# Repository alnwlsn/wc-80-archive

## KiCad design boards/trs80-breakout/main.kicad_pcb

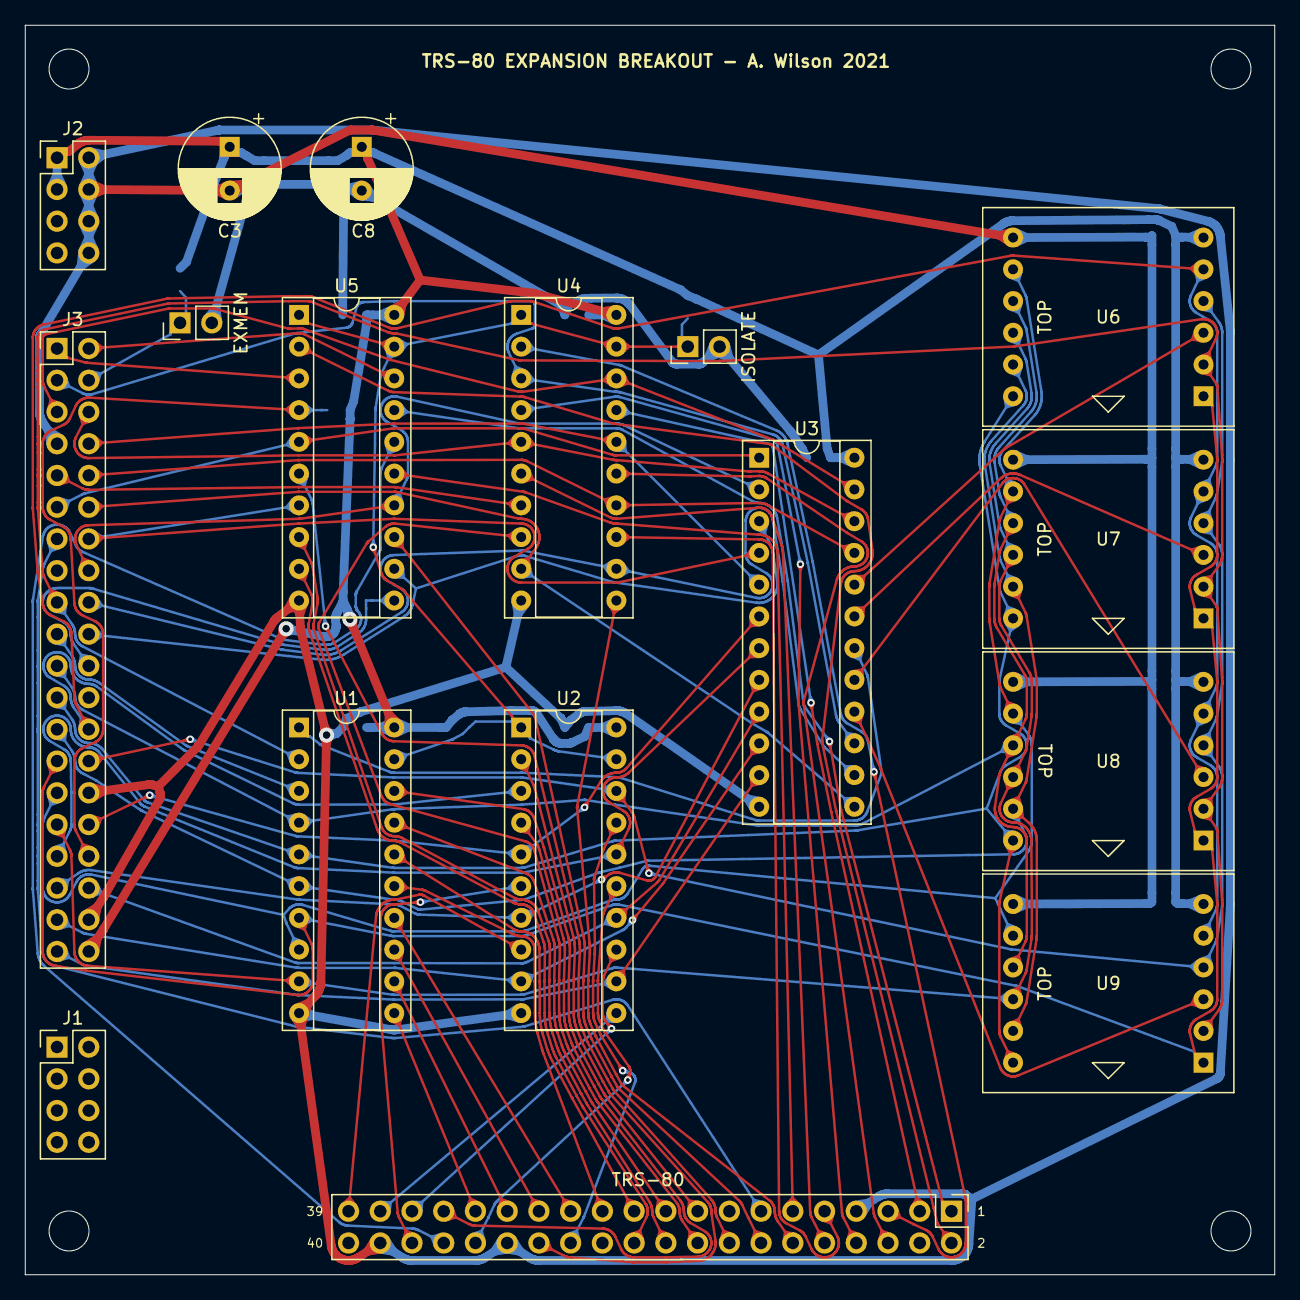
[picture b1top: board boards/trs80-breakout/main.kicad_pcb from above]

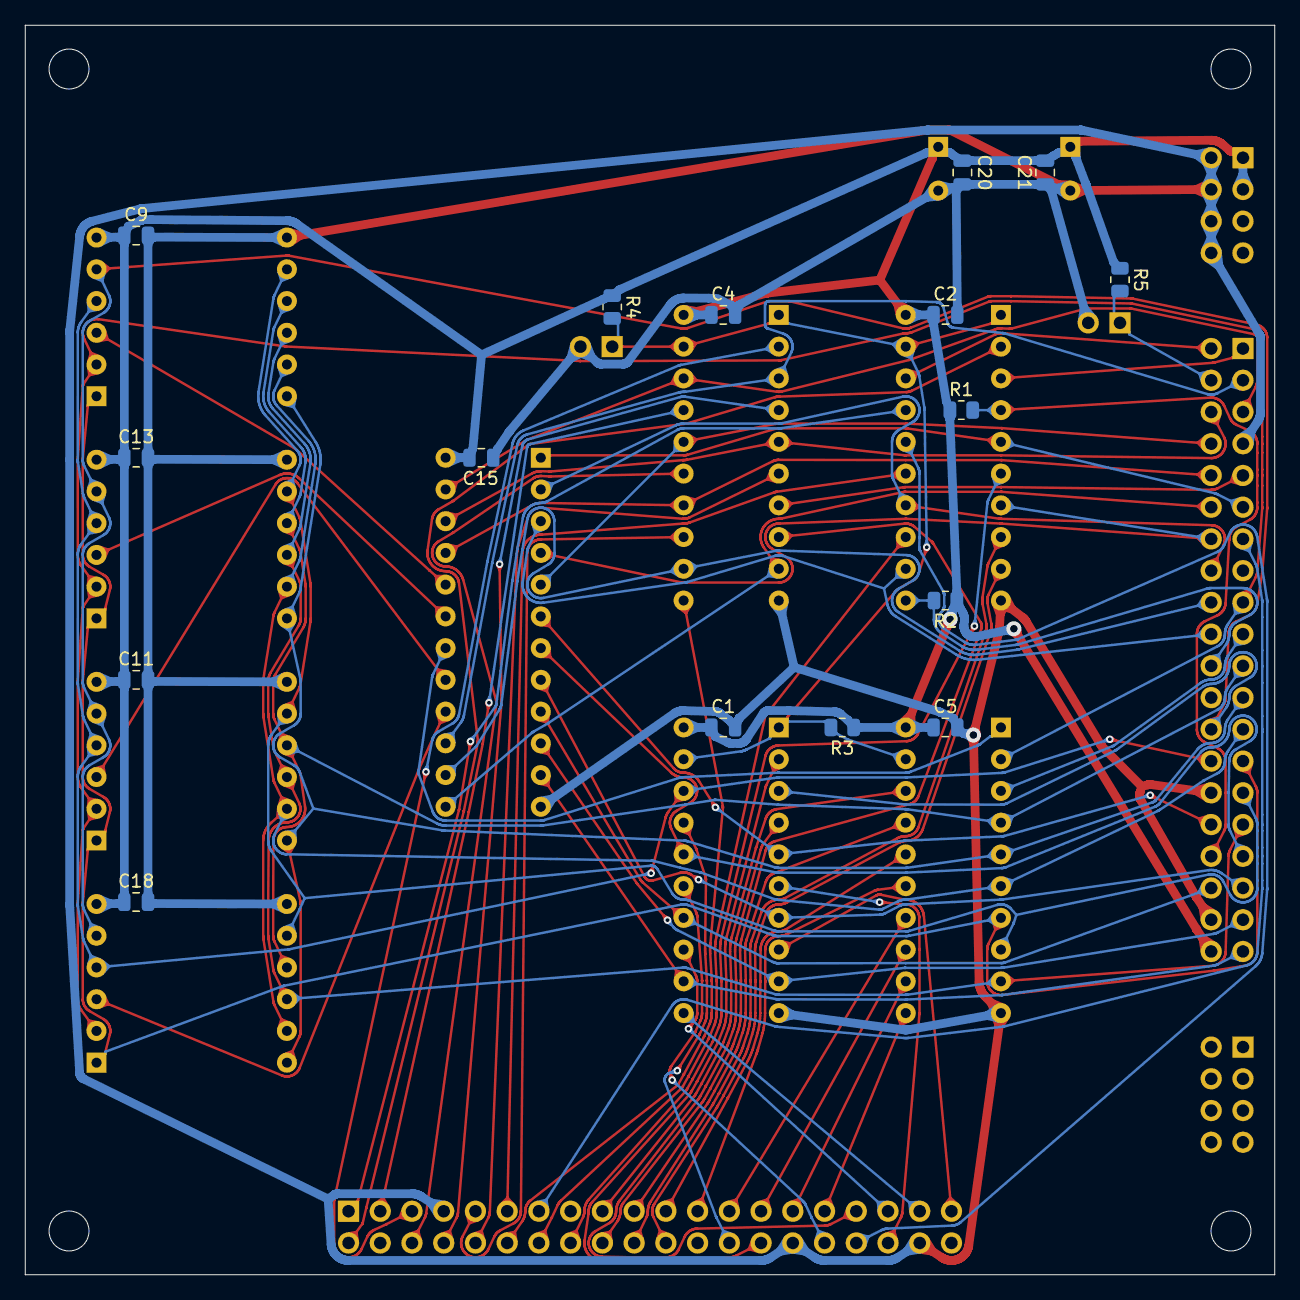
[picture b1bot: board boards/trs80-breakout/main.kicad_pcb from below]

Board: 2 copper layers, 100.0 x 100.0 mm, 37 parts (16 on the bottom side), 74 nets.

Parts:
C1, C2, C4, C5, C9, C11, C13, C15, C18, C20, C21: 100n; C_0805_2012Metric
C3, C8: 470uF; CP_Radial_D8.0mm_P3.50mm
J1, J2: Conn_02x04_Odd_Even; PinHeader_2x04_P2.54mm_Vertical
J3: TRS80W-header; PinHeader_2x20_P2.54mm_Vertical
J4: TRS-80; PinHeader_2x20_P2.54mm_Vertical
JP1: ISOLATE; PinHeader_1x02_P2.54mm_Vertical
JP2: EXMEM; PinHeader_1x02_P2.54mm_Vertical
M1, M2, M3, M4: 3mm-mounting-hole; MountingHole_3.2mm_M3_DIN965
R1, R2, R3, R4, R5: R; R_0805_2012Metric
U1: 74LS245; DIP-20_W7.62mm_Socket
U2, U4, U5: 74LS244; DIP-20_W7.62mm_Socket
U3: ATF22V10C; DIP-24_W7.62mm_Socket
U6, U7, U8, U9: HPDL1414; DIP-24_W15.24mm_Socket

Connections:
+5V: C1.1, C2.1, C3.1, C4.1, C5.1, C8.1, C9.1, C11.1, C13.1, C15.1, C18.1, C20.1, C21.1, J2.1, J2.3, J3.40, R1.1, R2.1, R3.1, R4.1, R5.1, U1.20, U2.20, U3.24, U4.20, U5.20, U6.6, U7.6, U8.6, U9.6
A0: J4.26, U2.17
A1: J4.28, U2.2
A2: J4.39, U2.8
A3: J4.33, U2.4
A4: J4.32, U2.15
A5: J4.36, U2.6
A6: J4.37, U2.11
A7: J4.35, U2.13
A8: J4.12, U4.11
A9: J4.18, U4.8
A10: J4.3, U4.17
A11: J4.10, U4.6
A12: J4.6, U4.15
A13: J4.5, U4.2
A14: J4.9, U4.13
A15: J4.8, U4.4
D0: J4.29, U1.12
D1: J4.21, U1.16
D2: J4.31, U1.11
D3: J4.25, U1.14
D4: J4.17, U1.18
D5: J4.27, U1.13
D6: J4.23, U1.15
D7: J4.19, U1.17
F_A0: J3.26, U2.3, U6.5, U7.5, U8.5, U9.5
F_A1: J3.28, U2.18, U6.4, U7.4, U8.4, U9.4
F_A2: J3.39, U2.12, U3.11
F_A3: J3.33, U2.16, U3.7
F_A4: J3.32, U2.5, U3.6
F_A5: J3.36, U2.14, U3.9
F_A6: J3.37, U2.9, U3.10
F_A7: J3.35, U2.7, U3.8
F_A8: J3.12, U3.13, U4.9
F_A9: J3.18, U3.14, U4.12
F_A10: J3.3, U3.15, U4.3
F_A11: J3.10, U3.21, U4.14
F_A12: J3.6, U3.22, U4.5
F_A13: J3.5, U3.23, U4.18
F_A14: J3.9, U4.7
F_A15: J3.8, U3.5, U4.16
F_D0: J3.29, U1.8, U6.8, U7.8, U8.8, U9.8
F_D1: J3.21, U1.4, U6.9, U7.9, U8.9, U9.9
F_D2: J3.31, U1.9, U6.10, U7.10, U8.10, U9.10
F_D3: J3.25, U1.6, U6.11, U7.11, U8.11, U9.11
F_D4: J3.17, U1.2, U6.2, U7.2, U8.2, U9.2
F_D5: J3.27, U1.7, U6.1, U7.1, U8.1, U9.1
F_D6: J3.23, U1.5, U6.12, U7.12, U8.12, U9.12
F_D7: J3.19, U1.3
GND: C1.2, C2.2, C3.2, C4.2, C5.2, C8.2, C9.2, C11.2, C13.2, C15.2, C18.2, C20.2, C21.2, J2.2, J2.4, J2.6, J2.8, J3.7, J3.30, J3.38, J4.7, J4.30, J4.38, JP1.2, JP2.2, U1.10, U2.10, U3.12, U4.10, U5.10, U6.7, U7.7, U8.7, U9.7
unnamed: U1.1, U3.18
S1: U3.16, U9.3
S2: U3.20, U6.3
S3: U3.17, U8.3
S4: U3.19, U7.3
~F_EXMEM~: J3.4, JP2.1, R5.2
~F_INTAK~: J3.13, J4.13
~F_INT~: J3.22, R2.2, U5.11
~F_IN~: J3.20, U3.3, U5.12
~F_MREQ~: J3.2, U5.18
~F_OUT~: J3.11, U3.1, U5.5
~F_READ~: J3.16, U3.2, U5.14
~F_SYSRES~: J3.1, U5.3
~F_WAIT~: J3.34, R1.2, U5.4
~F_WRITE~: J3.14, U3.4, U5.7
~INT~: J4.22, U5.9
~IN~: J4.20, U5.8
~ISOLATE~: JP1.1, R3.2, R4.2, U1.19, U2.1, U2.19, U4.1, U4.19, U5.1, U5.19
~MREQ~: J4.2, U5.2
~OUT~: J4.11, U5.15
~READ~: J4.16, U5.6
~SYSRES~: J4.1, U5.17
~WAIT~: J4.34, U5.16
~WRITE~: J4.14, U5.13

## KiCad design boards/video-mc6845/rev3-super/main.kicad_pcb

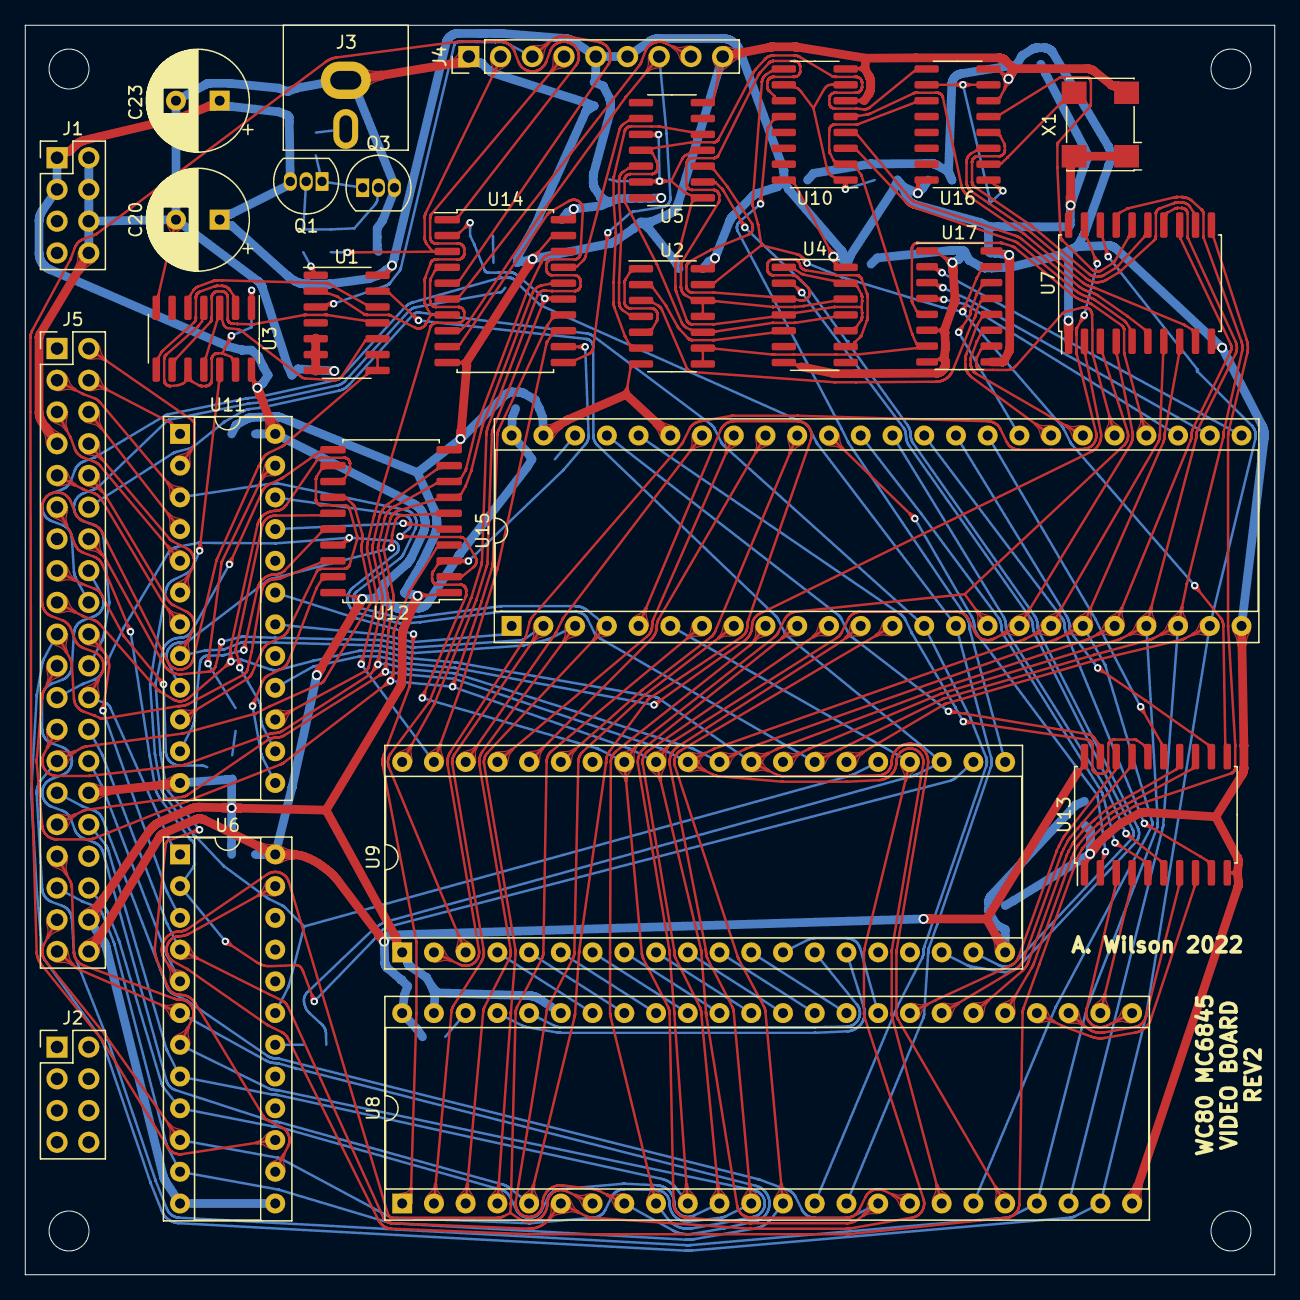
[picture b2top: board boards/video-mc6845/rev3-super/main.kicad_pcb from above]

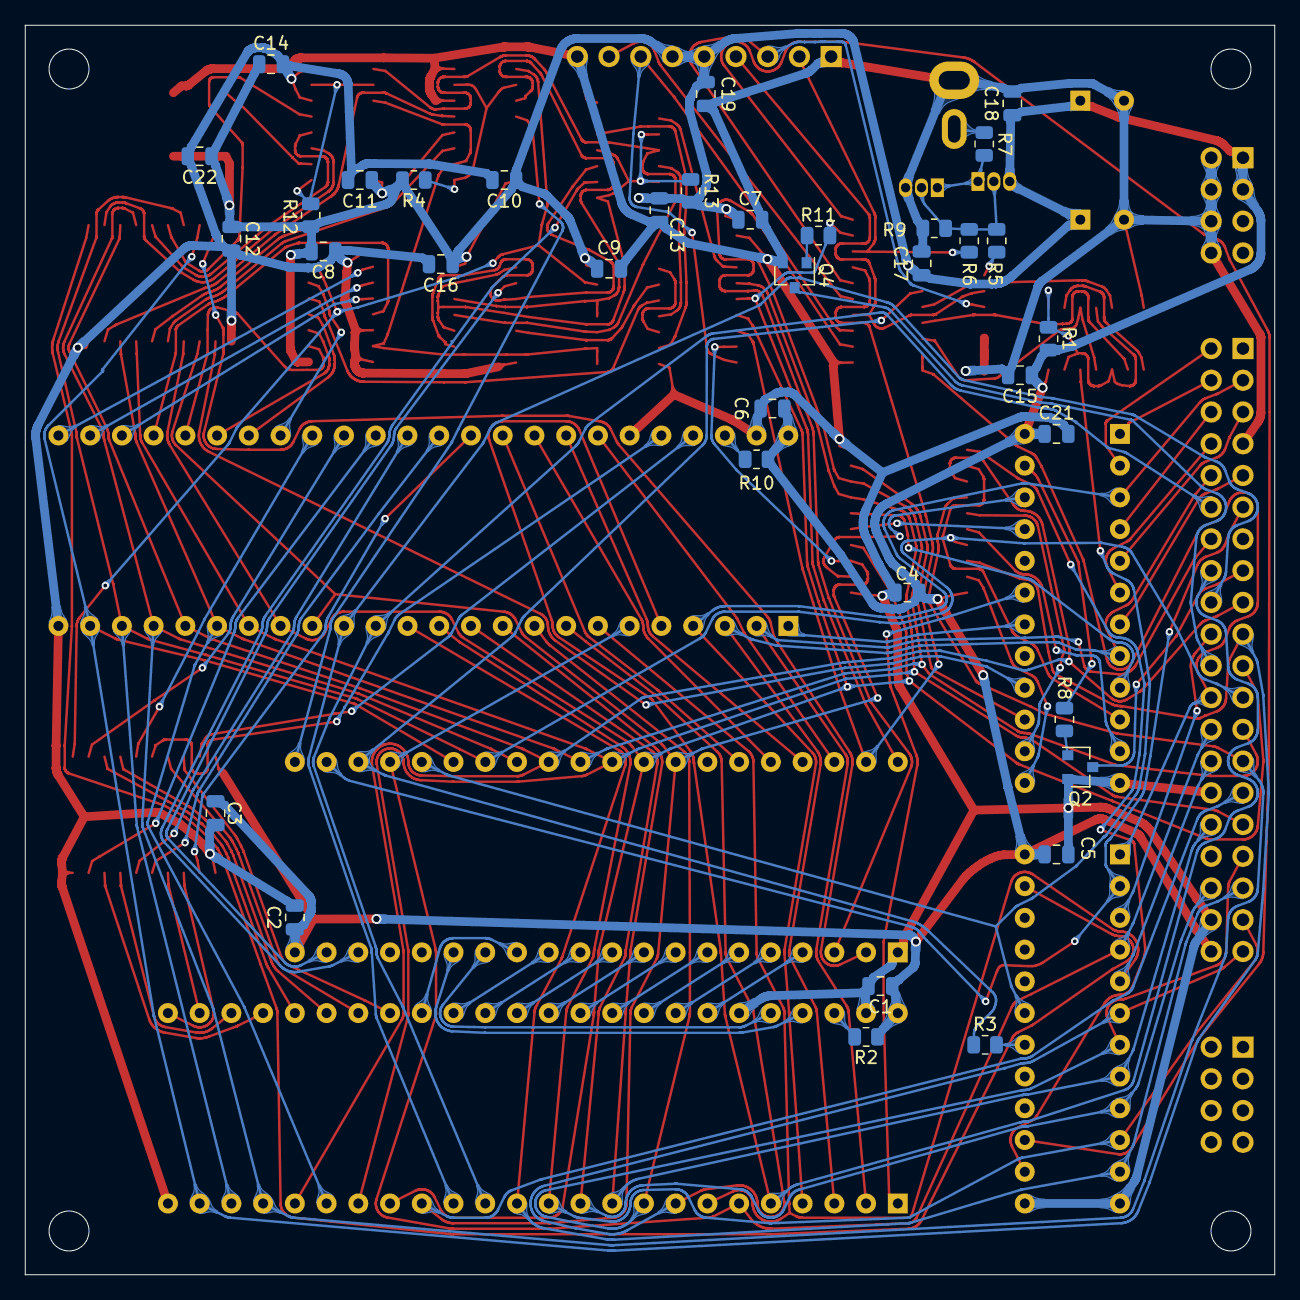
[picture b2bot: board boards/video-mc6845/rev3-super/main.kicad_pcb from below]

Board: 2 copper layers, 100.0 x 100.0 mm, 67 parts (36 on the bottom side), 139 nets.

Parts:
C1, C2, C3, C4, C5, C6, C7, C8, C9, C10, C11, C12, C13, C14, C15, C16, C17, C18, C19, C21, C22: 100n; C_0805_2012Metric
C20, C23: 470uF; CP_Radial_D8.0mm_P3.50mm
J1, J2: Conn_02x04_Odd_Even; PinHeader_2x04_P2.54mm_Vertical
J3: Conn_Coaxial; AV-5
J4: Conn_01x09_Male; PinHeader_1x09_P2.54mm_Vertical
J5: TRS80W-header; PinHeader_2x20_P2.54mm_Vertical
M1, M2, M3, M4: 3mm-mounting-hole; MountingHole_3.2mm_M3_DIN965
Q1: 2N3904; TO-92_Inline
Q2, Q4: BSS138; SOT-23
Q3: 2N3906; TO-92_Inline
R1, R2, R4, R10, R12, R13: 10K; R_0805_2012Metric
R3: optional; R_0805_2012Metric
R5: 910; R_0805_2012Metric
R6: 750; R_0805_2012Metric
R7: 75; R_0805_2012Metric
R8, R11: 100; R_0805_2012Metric
R9: 510; R_0805_2012Metric
U1, U2: 74LS02; SOIC-14_3.9x8.7mm_P1.27mm
U3, U4, U5: 74LS74; SOIC-14_3.9x8.7mm_P1.27mm
U6, U11: ATF22V10C; DIP-24_W7.62mm_Socket
U7, U12, U13: 74LS374; SOIC-20W_7.5x12.8mm_P1.27mm
U8: SCREENMEM; DIP-48_W15.24mm_Socket
U9: MC68B45; DIP-40_W15.24mm_Socket
U10, U16: 74LS163; SOIC-16_3.9x9.9mm_P1.27mm
U14: 74LS244; SOIC-20W_7.5x12.8mm_P1.27mm
U15: CHARROM; DIP-48_W15.24mm_Socket
U17: 74LS166; SO-16_3.9x9.9mm_P1.27mm
X1: SG-7050CAN; Oscillator_SMD_SeikoEpson_SG8002CA-4Pin_7.0x5.0mm

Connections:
74_PULL: R13.1, U4.1, U4.4, U4.10, U4.13, U5.1, U5.4, U5.10, U5.13
+5V: C1.1, C2.1, C3.1, C4.1, C5.1, C6.1, C7.1, C8.1, C9.1, C10.1, C11.1, C12.1, C13.1, C14.1, C15.1, C16.1, C17.1, C18.1, C19.1, C20.1, C21.1, C22.1, C23.1, J1.1, J1.3, J4.5, J4.6, J5.40, Q1.3, R1.2, R2.1, R4.2, R10.2, R12.2, R13.2, U1.14, U2.14, U3.14, U4.14, U5.14, U6.24, U7.20, U8.48, U9.20, U10.16, U11.24, U12.20, U13.20, U14.20, U15.48, U16.16, U17.9, U17.16, X1.1, X1.4
/CA0: U13.2, U15.38
/CA1: U13.5, U15.37
/CA2: U13.6, U15.36
/CA3: U13.9, U15.35
/CA4: U13.12, U15.34
/CA5: U13.15, U15.33
/CA6: U13.16, U15.44
/CA7: U13.19, U15.45
/CD0: U15.25, U17.2
/CD1: U15.26, U17.3
/CD2: U15.27, U17.4
/CD3: U15.28, U17.5
/CD4: U15.29, U17.10
/CD5: U15.30, U17.11
/CD6: U15.31, U17.12
/CD7: U15.32, U17.14
/CL74PU2: R1.1, U3.1, U3.4, U3.10, U3.13
/CRPU: R10.1, U15.46
/CURSOR: U2.2, U4.5
/CURSU: U4.2, U9.19
/DEU: U5.2, U9.18
/DIV1PU: R4.1, U10.1, U10.7, U10.10
/DIV2PU: R12.1, U16.1, U16.7, U16.10
/HSB: J4.4, U1.2, U14.7
/IMGU: U2.4, U5.12
/IUR: Q2.1, R8.1
/IUU: R8.2, U11.23
/LPBU: J4.8, U14.6
/LPU: J4.7, U14.8, U14.11
/MA0: U8.42, U9.4
/MA1: U8.41, U9.5
/MA2: U8.40, U9.6
/MA3: U8.39, U9.7
/MA4: U8.38, U9.8
/MA5: U8.37, U9.9
/MA6: U8.36, U9.10
/MA7: U8.35, U9.11
/MA8: U8.34, U9.12
/MA9: U8.33, U9.13
/MA10: U8.44, U9.14
/MA11: U8.45, U9.15
/NIMAGE: J4.2, R6.2, U14.3
/NOU: Q1.1, Q3.1, R7.2
/NOUT: J3.1, R7.1
/NSYNC: R5.2, U1.1
/NVDC: Q1.2, Q3.2, R5.1, R6.1, R9.2
/OMCS: R3.2, U6.18
/RA0: U9.38, U15.42
/RA1: U9.37, U15.41
/RA2: U9.36, U15.40
/RA3: U9.35, U15.39
/SD0: U8.25, U13.3
/SD1: U8.26, U13.4
/SD2: U8.27, U13.7
/SD3: U8.28, U13.8
/SD4: U8.29, U13.13
/SD5: U8.30, U13.14
/SD6: U8.31, U13.17
/SD7: U8.32, U13.18
/SRPU: R2.2, U8.46
/VSB: J4.3, U1.3, U14.5
/VSR: Q4.1, R11.1
/~DISPEN~: U2.6, U5.5
ADR0: U11.10, U12.12
ADR1: U11.14, U12.15
ADR2: U11.11, U12.16
ADR3: U11.13, U12.19
CHARCLOCK: U2.13, U10.9, U13.11, U17.15
CRTCCLOCK: U9.21, U10.12
DC0: U7.12, U16.3
DC1: U7.15, U16.4
DC2: U7.16, U16.5
DOTCLOCK: U2.8, U2.9, U10.2, U16.11, U17.7
F_A0: J5.26, U6.4, U8.6, U9.24, U15.6
F_A1: J5.28, U6.5, U8.7, U15.7
F_A2: J5.39, U6.6, U8.8, U15.8
F_A3: J5.33, U6.7, U8.9, U15.9
F_A4: J5.32, U6.8, U8.10, U15.10
F_A5: J5.36, U6.9, U8.11, U15.11
F_A6: J5.37, U6.10, U8.12, U15.12
F_A7: J5.35, U6.11, U8.13, U15.13
F_A8: J5.12, U8.14, U15.14
F_A9: J5.18, U8.15, U15.15
F_A10: J5.3, U8.4, U11.3, U15.4
F_A11: J5.10, U8.3, U11.8, U15.3
F_A12: J5.6, U11.4
F_A13: J5.5, U11.5
F_A14: J5.9, U11.7
F_A15: J5.8, U11.6
F_D0: J5.29, U7.3, U8.16, U9.33, U12.3, U14.12, U15.16
F_D1: J5.21, U7.4, U8.17, U9.32, U12.4, U14.14, U15.17
F_D2: J5.31, U7.7, U8.18, U9.31, U12.7, U14.16, U15.18
F_D3: J5.25, U7.8, U8.19, U9.30, U12.8, U14.18, U15.19
F_D4: J5.17, U7.13, U8.20, U9.29, U12.13, U15.20
F_D5: J5.27, U7.14, U8.21, U9.28, U12.14, U15.21
F_D6: J5.23, U7.17, U8.22, U9.27, U12.17, U15.22
F_D7: J5.19, U7.18, U8.23, U9.26, U12.18, U15.23
GND: C1.2, C2.2, C3.2, C4.2, C5.2, C6.2, C7.2, C8.2, C9.2, C10.2, C11.2, C12.2, C13.2, C14.2, C15.2, C16.2, C17.2, C18.2, C19.2, C20.2, C21.2, C22.2, C23.2, J1.2, J1.4, J1.6, J1.8, J3.2, J4.1, J4.9, J5.7, J5.30, J5.38, Q2.2, Q3.3, Q4.2, R9.1, U1.5, U1.6, U1.7, U2.7, U3.7, U4.7, U5.7, U6.12, U6.13, U7.1, U7.10, U8.24, U8.43, U8.47, U9.1, U10.6, U10.8, U11.12, U12.1, U12.10, U13.1, U13.10, U14.10, U14.19, U15.24, U15.43, U15.47, U16.6, U16.8, U17.1, U17.6, U17.8, X1.2
HS: U9.39, U14.4, U14.13
IMAGE: U5.9, U14.17
LIGHTPEN: U9.3, U14.9
MC6845E: R3.1, U1.13, U9.23
MSK0: U11.22, U12.2
MSK1: U11.21, U12.5
MSK2: U11.9, U12.6
MSK3: U11.15, U12.9
unnamed: U1.10, U3.3, U3.11
unnamed: U1.11, U3.9
unnamed: U1.12, U3.5
unnamed: U2.1, U2.5
unnamed: U3.2, U3.8
unnamed: U4.3, U4.9, U5.3
unnamed: U2.11, U2.12, U4.12, U10.11
unnamed: U16.2, X1.3
unnamed: U2.3, U17.13
OPT8: U7.2, U11.16
OPTIONS1: U6.14, U12.11
OPTIONS2: U6.23, U7.11
PL0: U7.5, U10.3
PL1: U7.6, U10.4
PL2: U7.9, U10.5
VIDSTAT: U6.15, U14.1
VS: R11.2, U9.40, U14.2, U14.15
Z80CLK: J5.24, U1.8, U1.9, U6.1
~CRMEM~: U11.18, U15.1
~DOTCLOCK~: U2.10, U4.11, U5.11, U16.9
~EXMEM~: J5.4, U11.1
~F_IN~: J5.20, U6.3
~F_OUT~: J5.11, U6.2, U9.22
~F_RD~: J5.16, U8.5, U15.5
~F_WR~: J5.14, U8.2, U15.2
~INT~: J5.22, Q4.3
~INUSE~: J5.15, Q2.3
~MC6845CS~: U3.12, U6.19, U9.25
~MEMRQ~: J5.2, U11.2
~SCMEM~: U8.1, U11.19
~SYSRES~: U7.19, U9.2

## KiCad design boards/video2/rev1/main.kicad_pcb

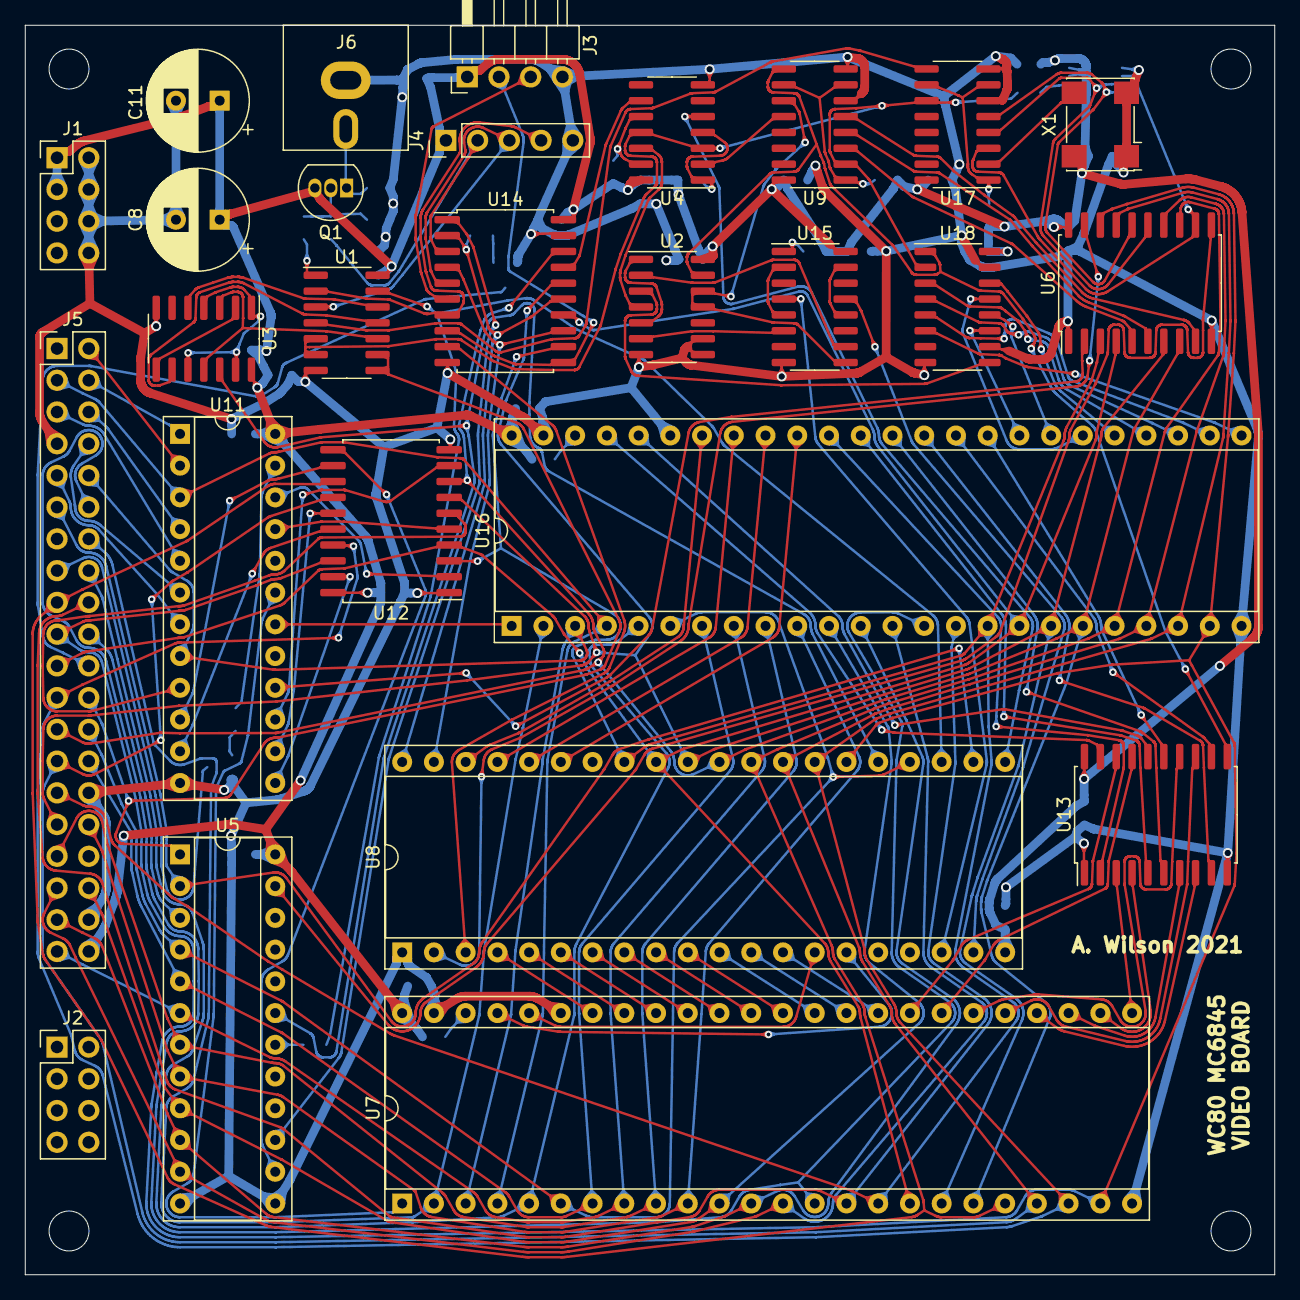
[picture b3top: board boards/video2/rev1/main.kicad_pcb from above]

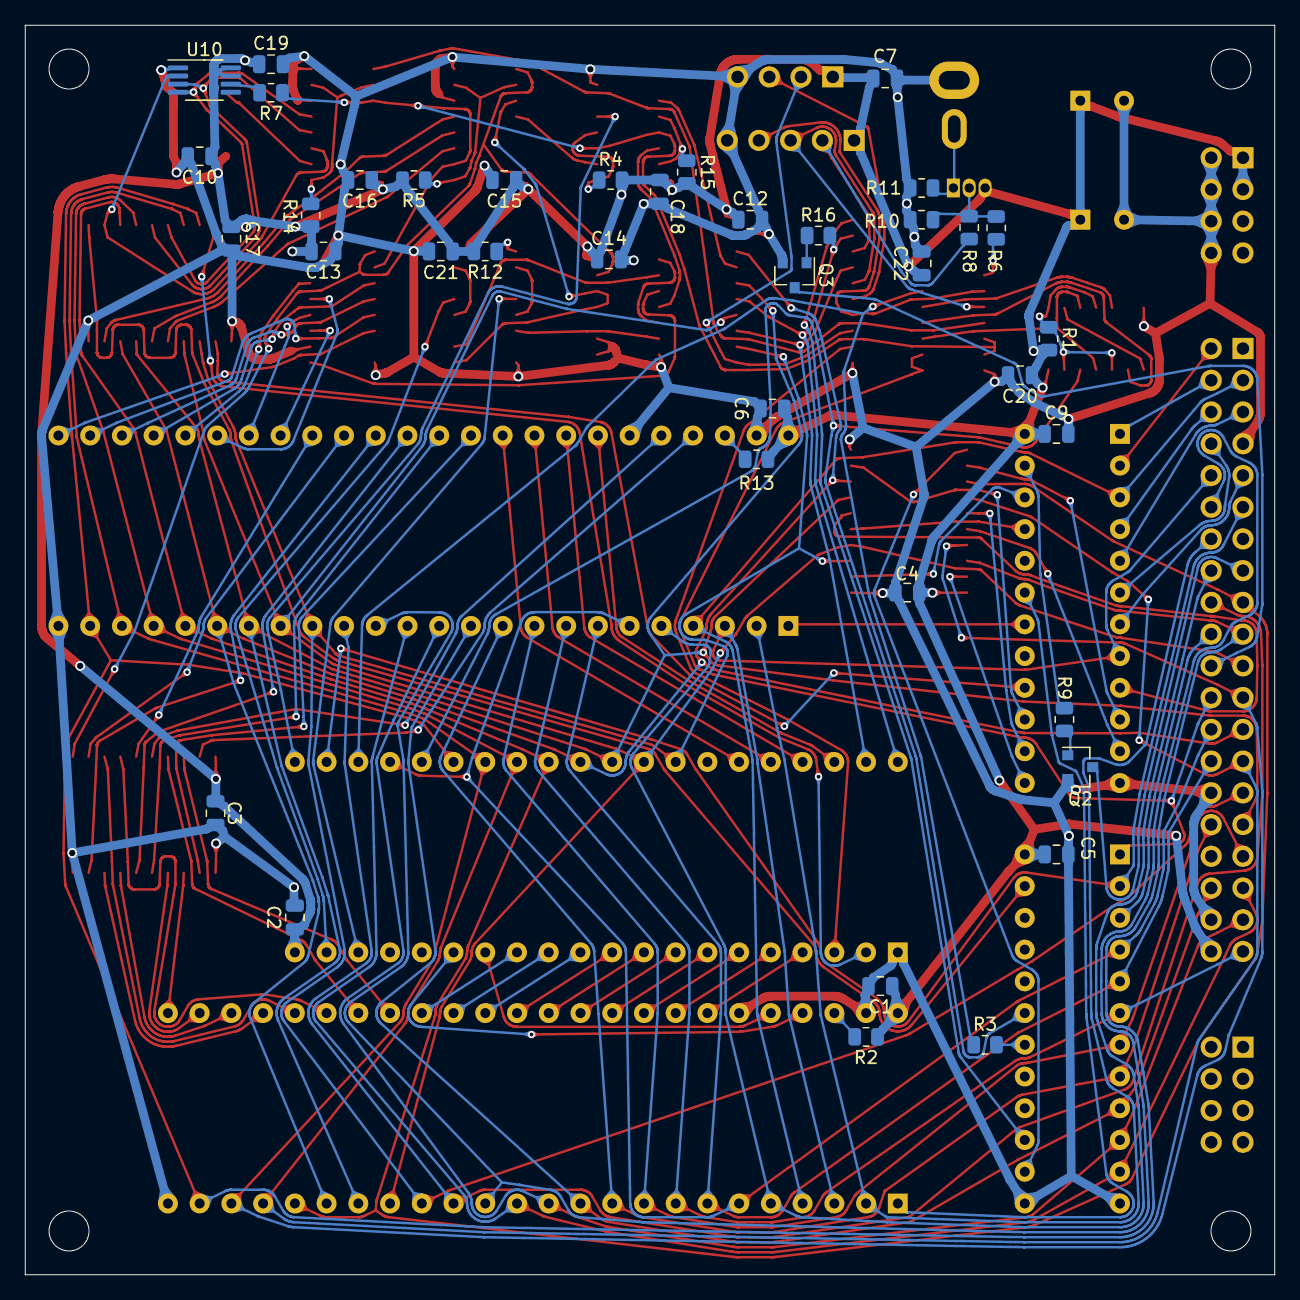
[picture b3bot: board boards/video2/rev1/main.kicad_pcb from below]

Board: 2 copper layers, 100.0 x 100.0 mm, 70 parts (39 on the bottom side), 143 nets.

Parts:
C1, C2, C3, C4, C5, C6, C7, C9, C10, C12, C13, C14, C15, C16, C17, C18, C19, C20, C21, C22: 100n; C_0805_2012Metric
C8, C11: 470uF; CP_Radial_D8.0mm_P3.50mm
J1, J2: Conn_02x04_Odd_Even; PinHeader_2x04_P2.54mm_Vertical
J3: LIGHT_PEN; PinHeader_1x04_P2.54mm_Horizontal
J4: CRT_SIGNALS; PinHeader_1x05_P2.54mm_Vertical
J5: TRS80W-header; PinHeader_2x20_P2.54mm_Vertical
J6: Conn_Coaxial; AV-5
M1, M2, M3, M4: 3mm-mounting-hole; MountingHole_3.2mm_M3_DIN965
Q1: 2N3904; TO-92_Inline
Q2, Q3: BSS138; SOT-23
R1, R2, R4, R5, R12, R13, R14, R15: 10K; R_0805_2012Metric
R3: optional; R_0805_2012Metric
R6: 1800; R_0805_2012Metric
R7: 10; R_0805_2012Metric
R8: 2000; R_0805_2012Metric
R9, R16: 100; R_0805_2012Metric
R10, R11: 470; R_0805_2012Metric
U1, U2: 74LS02; SOIC-14_3.9x8.7mm_P1.27mm
U3, U4: 74LS74; SOIC-14_3.9x8.7mm_P1.27mm
U5, U11: ATF22V10C; DIP-24_W7.62mm_Socket
U6, U12, U13: 74LS374; SOIC-20W_7.5x12.8mm_P1.27mm
U7: SCREENMEM; DIP-48_W15.24mm_Socket
U8: MC68B45; DIP-40_W15.24mm_Socket
U9, U17: 74LS163; SOIC-16_3.9x9.9mm_P1.27mm
U10: LTC6903; MSOP-8_3x3mm_P0.65mm
U14: 74LS244; SOIC-20W_7.5x12.8mm_P1.27mm
U15: 74LS175; SOIC-16_3.9x9.9mm_P1.27mm
U16: CHARROM; DIP-48_W15.24mm_Socket
U18: 74LS165; SO-16_3.9x9.9mm_P1.27mm
X1: SG-7050CAN; Oscillator_SMD_SeikoEpson_SG8002CA-4Pin_7.0x5.0mm

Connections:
+5V: C1.1, C2.1, C3.1, C4.1, C5.1, C6.1, C7.1, C8.1, C9.1, C10.1, C11.1, C12.1, C13.1, C14.1, C15.1, C16.1, C17.1, C18.1, C19.1, C20.1, C21.1, C22.1, J1.1, J1.3, J3.1, J4.1, J5.40, Q1.3, R1.2, R2.1, R4.2, R5.2, R12.2, R13.2, R14.2, R15.2, U1.14, U2.14, U3.14, U4.14, U5.24, U6.20, U7.48, U8.20, U9.16, U10.7, U10.8, U11.24, U12.20, U13.20, U14.20, U15.16, U16.48, U17.16, U18.16, X1.4
/CURSOR: U2.2, U15.10
/~DISPEN~: U2.6, U15.6
CHARCLOCK: U2.13, U9.9, U13.11, U18.1
CRTCCLOCK: U4.5, U8.21
DC0: U6.12, U10.2, U17.3
DC1: U6.15, U10.3, U17.4
DC2: U6.16, U10.4, U17.5
DOTCLOCK: R7.1, U1.5, U1.6, U4.3, U4.11, U9.2, U17.11, U18.2
F_A0: J5.26, U5.4, U7.6, U8.24, U16.6
F_A1: J5.28, U5.5, U7.7, U16.7
F_A2: J5.39, U5.6, U7.8, U16.8
F_A3: J5.33, U5.7, U7.9, U16.9
F_A4: J5.32, U5.8, U7.10, U16.10
F_A5: J5.36, U5.9, U7.11, U16.11
F_A6: J5.37, U5.10, U7.12, U16.12
F_A7: J5.35, U5.11, U7.13, U16.13
F_A8: J5.12, U7.14, U16.14
F_A9: J5.18, U7.15, U16.15
F_A10: J5.3, U7.4, U11.3, U16.4
F_A11: J5.10, U7.3, U11.8, U16.3
F_A12: J5.6, U11.4
F_A13: J5.5, U11.5
F_A14: J5.9, U11.7
F_A15: J5.8, U11.6
F_D0: J5.29, U6.3, U7.16, U8.33, U12.3, U14.12, U16.16
F_D1: J5.21, U6.4, U7.17, U8.32, U12.4, U14.14, U16.17
F_D2: J5.31, U6.7, U7.18, U8.31, U12.7, U14.16, U16.18
F_D3: J5.25, U6.8, U7.19, U8.30, U12.8, U14.18, U16.19
F_D4: J5.17, U6.13, U7.20, U8.29, U12.13, U16.20
F_D5: J5.27, U6.14, U7.21, U8.28, U12.14, U16.21
F_D6: J5.23, U6.17, U7.22, U8.27, U12.17, U16.22
F_D7: J5.19, U6.18, U7.23, U8.26, U12.18, U16.23
GND: C1.2, C2.2, C3.2, C4.2, C5.2, C6.2, C7.2, C8.2, C9.2, C10.2, C11.2, C12.2, C13.2, C14.2, C15.2, C16.2, C17.2, C18.2, C19.2, C20.2, C21.2, C22.2, J1.2, J1.4, J1.6, J1.8, J3.4, J4.5, J5.7, J5.30, J5.38, J6.2, Q2.2, Q3.2, R10.1, R11.1, U1.7, U2.7, U2.8, U2.9, U3.7, U4.7, U5.12, U5.13, U6.1, U6.10, U7.24, U7.43, U7.47, U8.1, U9.6, U9.8, U10.1, U11.12, U12.1, U12.10, U13.1, U13.10, U14.10, U14.19, U15.8, U16.24, U16.43, U16.47, U17.6, U17.8, U18.8, U18.10, U18.15, X1.1, X1.2
HS: U8.39, U14.4, U14.13
IMAGE: U4.9, U14.17
LIGHTPEN: U8.3, U14.9
MC6845E: R3.1, U1.13, U8.23
unnamed: J3.2, U14.8, U14.11
unnamed: J3.3, U14.6
unnamed: J4.2, R8.2, U14.3
unnamed: J4.3, U1.3, U14.5
unnamed: J4.4, U1.2, U14.7
unnamed: J6.1, Q1.1, R11.2
unnamed: Q1.2, R6.1, R8.1, R10.2
unnamed: Q2.1, R9.1
unnamed: Q3.1, R16.1
unnamed: R1.1, U3.1, U3.4, U3.10, U3.13
unnamed: R2.2, U7.46
unnamed: R3.2, U5.18
unnamed: R4.1, U4.1, U4.4
unnamed: R5.1, U9.1, U9.7, U9.10
unnamed: R6.2, U1.1
unnamed: R7.2, U10.6
unnamed: R9.2, U11.23
unnamed: R12.1, U15.1
unnamed: R13.1, U16.46
unnamed: R14.1, U17.1, U17.7, U17.10
unnamed: R15.1, U4.10, U4.13
unnamed: U1.4, U17.9
unnamed: U1.10, U3.3, U3.11
unnamed: U1.11, U3.9
unnamed: U1.12, U3.5
unnamed: U2.1, U2.5
unnamed: U2.4, U4.12
unnamed: U3.2, U3.8
unnamed: U4.2, U9.12
unnamed: U7.33, U8.13
unnamed: U7.34, U8.12
unnamed: U7.35, U8.11
unnamed: U7.36, U8.10
unnamed: U7.37, U8.9
unnamed: U7.38, U8.8
unnamed: U7.39, U8.7
unnamed: U7.40, U8.6
unnamed: U7.41, U8.5
unnamed: U7.42, U8.4
unnamed: U7.44, U8.14
unnamed: U7.45, U8.15
unnamed: U13.2, U16.38
unnamed: U7.25, U13.3
unnamed: U7.26, U13.4
unnamed: U13.5, U16.37
unnamed: U13.6, U16.36
unnamed: U7.27, U13.7
unnamed: U7.28, U13.8
unnamed: U13.9, U16.35
unnamed: U13.12, U16.34
unnamed: U7.29, U13.13
unnamed: U7.30, U13.14
unnamed: U13.15, U16.33
unnamed: U13.16, U16.44
unnamed: U7.31, U13.17
unnamed: U7.32, U13.18
unnamed: U13.19, U16.45
unnamed: U15.2, U15.5
unnamed: U8.18, U15.4
unnamed: U2.11, U2.12, U9.11, U15.9
unnamed: U15.12, U15.15
unnamed: U8.19, U15.13
unnamed: U16.25, U18.6
unnamed: U16.26, U18.5
unnamed: U16.27, U18.4
unnamed: U16.28, U18.3
unnamed: U16.29, U18.14
unnamed: U16.30, U18.13
unnamed: U16.31, U18.12
unnamed: U16.32, U18.11
unnamed: U8.35, U16.39
unnamed: U8.36, U16.40
unnamed: U8.37, U16.41
unnamed: U8.38, U16.42
unnamed: U17.2, X1.3
unnamed: U2.3, U18.9
OPT0: U11.22, U12.2
OPT1: U11.21, U12.5
OPT2: U11.9, U12.6
OPT3: U11.15, U12.9
OPT4: U11.10, U12.12
OPT5: U11.14, U12.15
OPT6: U11.11, U12.16
OPT7: U11.13, U12.19
OPT8: U6.2, U11.16
OPTIONS1: U5.14, U12.11
OPTIONS2: U5.23, U6.11
PL0: U6.5, U9.3
PL1: U6.6, U9.4
PL2: U6.9, U9.5
VIDSTAT: U5.15, U14.1
VS: R16.2, U8.40, U14.2, U14.15
Z80CLK: J5.24, U1.8, U1.9, U5.1
~CRMEM~: U11.18, U16.1
~EXMEM~: J5.4, U11.1
~F_IN~: J5.20, U5.3
~F_OUT~: J5.11, U5.2, U8.22
~F_RD~: J5.16, U7.5, U16.5
~F_WR~: J5.14, U7.2, U16.2
~INT~: J5.22, Q3.3
~INUSE~: J5.15, Q2.3
~MC6845CS~: U3.12, U5.19, U8.25
~MEMRQ~: J5.2, U11.2
~SCMEM~: U7.1, U11.19
~SYSRES~: U6.19, U8.2
